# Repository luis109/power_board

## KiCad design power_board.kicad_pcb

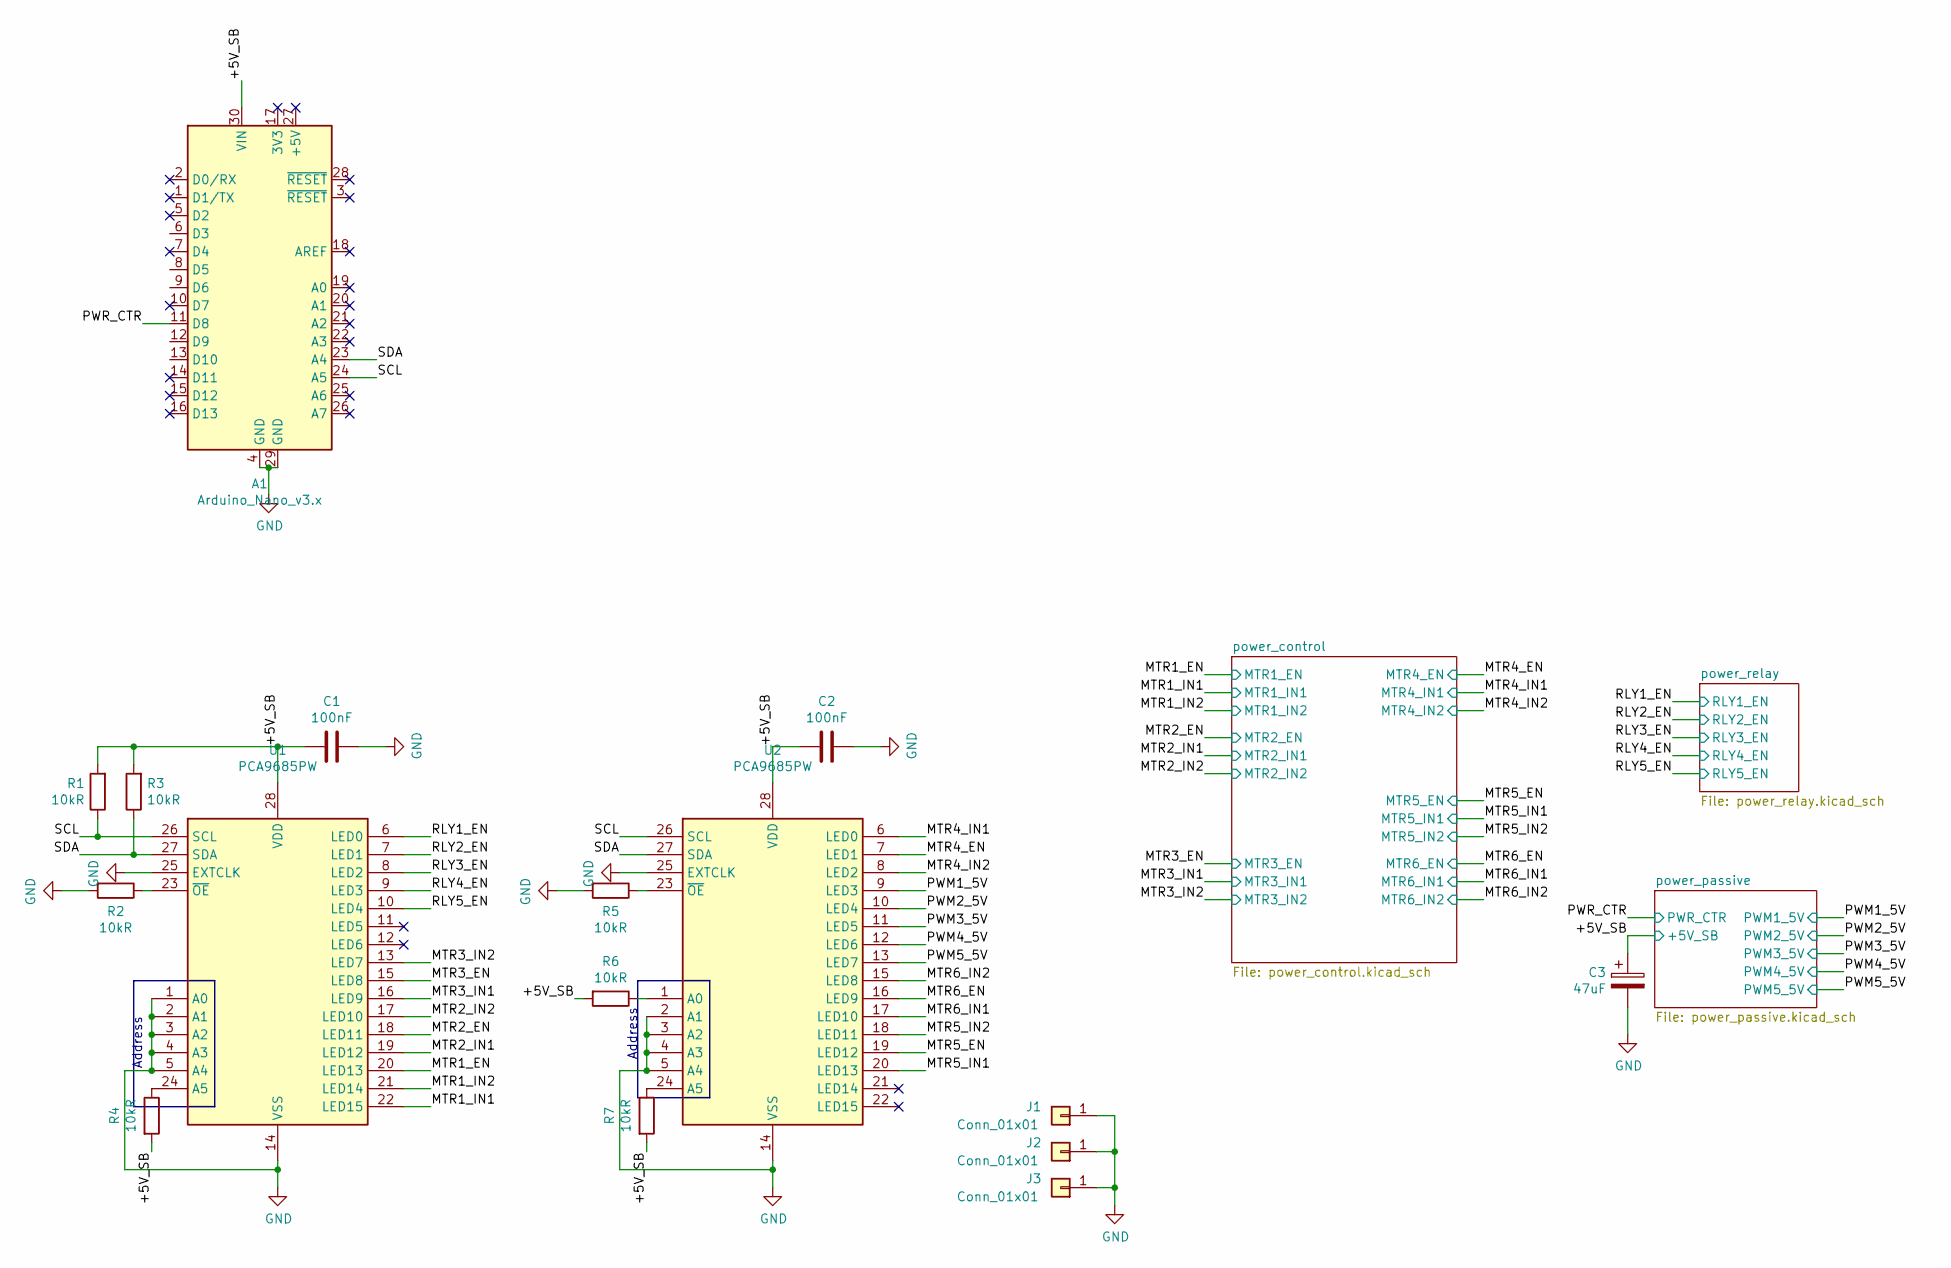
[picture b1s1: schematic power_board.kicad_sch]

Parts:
A1: Arduino_Nano_v3.x; Arduino_Nano
C1, C2: 100nF; C_0603
C3: 47uF; CP_Radial_D5.0mm_P2.00mm
J1, J2, J3: Conn_01x01; MountingHole_3.5mm_Pad
R1, R2, R3, R4, R5, R6, R7: 10kR; R_0603
U1, U2: PCA9685PW; TSSOP-28_4.4x9.7mm_P0.65mm

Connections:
/+5V_SB: A1.30 (VIN), C1.2, C2.2, C3.1, R1.2, R3.2, R4.2, R6.2, R7.2, U1.28 (VDD), U2.28 (VDD); also elsewhere on the board
/MTR1_EN: U1.20 (LED13); also elsewhere on the board
/MTR1_IN1: U1.22 (LED15); also elsewhere on the board
/MTR1_IN2: U1.21 (LED14); also elsewhere on the board
/MTR2_EN: U1.18 (LED11); also elsewhere on the board
/MTR2_IN1: U1.19 (LED12); also elsewhere on the board
/MTR2_IN2: U1.17 (LED10); also elsewhere on the board
/MTR3_EN: U1.15 (LED8); also elsewhere on the board
/MTR3_IN1: U1.16 (LED9); also elsewhere on the board
/MTR3_IN2: U1.13 (LED7); also elsewhere on the board
/MTR4_EN: U2.7 (LED1); also elsewhere on the board
/MTR4_IN1: U2.6 (LED0); also elsewhere on the board
/MTR4_IN2: U2.8 (LED2); also elsewhere on the board
/MTR5_EN: U2.19 (LED12); also elsewhere on the board
/MTR5_IN1: U2.20 (LED13); also elsewhere on the board
/MTR5_IN2: U2.18 (LED11); also elsewhere on the board
/MTR6_EN: U2.16 (LED9); also elsewhere on the board
/MTR6_IN1: U2.17 (LED10); also elsewhere on the board
/MTR6_IN2: U2.15 (LED8); also elsewhere on the board
/PWM1_5V: U2.9 (LED3); also elsewhere on the board
/PWM2_5V: U2.10 (LED4); also elsewhere on the board
/PWM3_5V: U2.11 (LED5); also elsewhere on the board
/PWM4_5V: U2.12 (LED6); also elsewhere on the board
/PWM5_5V: U2.13 (LED7); also elsewhere on the board
/PWR_CTR: A1.11 (D8); also elsewhere on the board
/RLY1_EN: U1.6 (LED0); also elsewhere on the board
/RLY2_EN: U1.7 (LED1); also elsewhere on the board
/RLY3_EN: U1.8 (LED2); also elsewhere on the board
/RLY4_EN: U1.9 (LED3); also elsewhere on the board
/RLY5_EN: U1.10 (LED4); also elsewhere on the board
/SCL: A1.24 (A5), R1.1, U1.26 (SCL), U2.26 (SCL)
/SDA: A1.23 (A4), R3.1, U1.27 (SDA), U2.27 (SDA)
GND: A1.4 (GND), A1.29 (GND), C1.1, C2.1, C3.2, J1.1, J2.1, J3.1, R2.2, R5.2, U1.1 (A0), U1.2 (A1), U1.3 (A2), U1.4 (A3), U1.5 (A4), U1.14 (VSS), U1.25 (EXTCLK), U2.2 (A1), U2.3 (A2), U2.4 (A3), U2.5 (A4), U2.14 (VSS), U2.25 (EXTCLK); also elsewhere on the board
unnamed: R2.1, U1.23 (~OE)
unnamed: R4.1, U1.24 (A5)
unnamed: R5.1, U2.23 (~OE)
unnamed: R6.1, U2.1 (A0)
unnamed: R7.1, U2.24 (A5)

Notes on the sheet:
Address

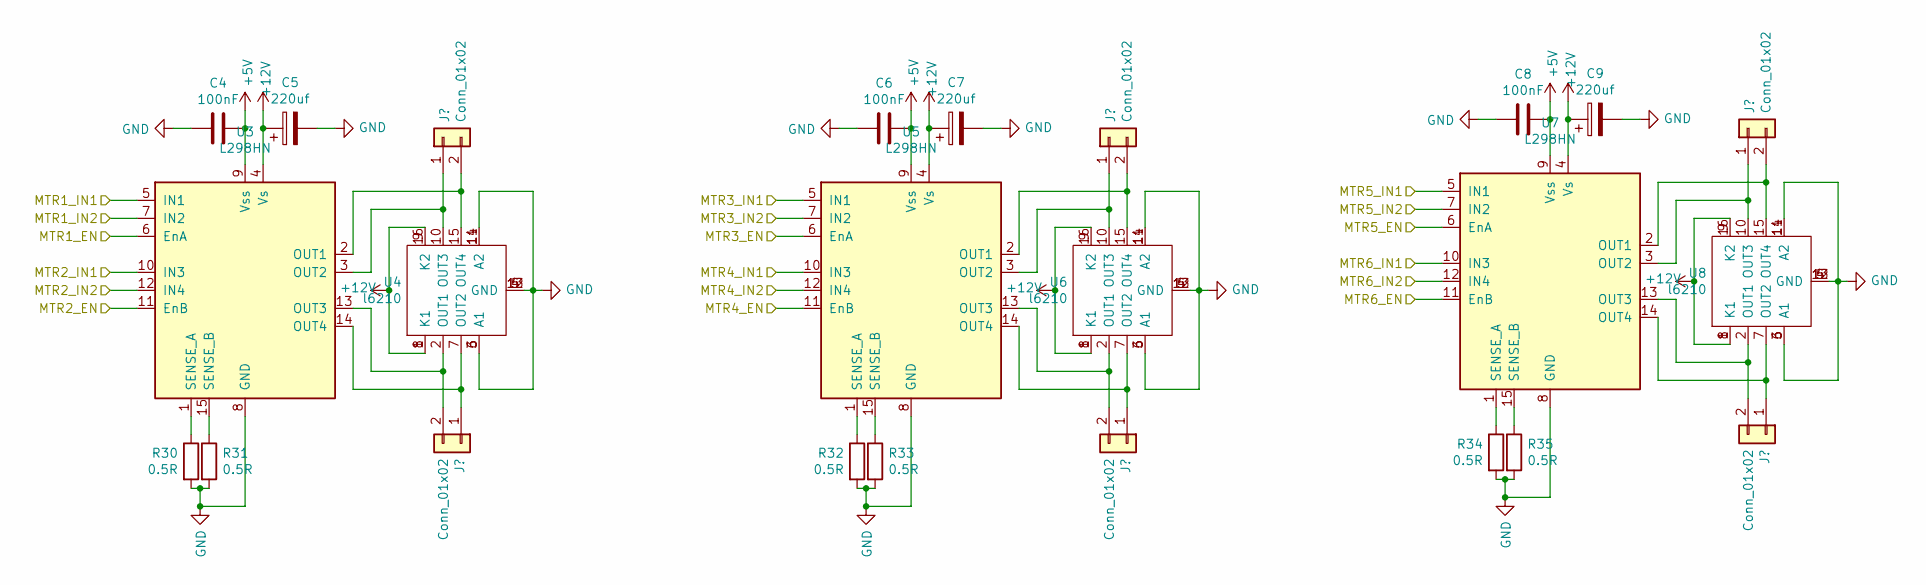
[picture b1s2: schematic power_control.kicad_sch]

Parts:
C4, C6, C8: 100nF; C_0603
C5, C7, C9: 220uf; CP_Radial_D10.0mm_P5.00mm
J25, J26, J27, J28, J29, J30: Conn_01x02; Molex_Micro-Fit_3.0_43045-0212_2x01_P3.00mm_Vertical
R30, R31, R32, R33, R34, R35: 0.5R; R_0805
U3, U5, U7: L298HN; TO-220-15_P2.54x2.54mm_StaggerOdd_Lead4.58mm_Vertical
U4, U6, U8: l6210; DIP-16_W7.62mm

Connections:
+5V: C4.1, C6.1, C8.1, U3.9 (Vss), U5.9 (Vss), U7.9 (Vss); also elsewhere on the board
+12V: C5.1, C7.1, C9.1, U3.4 (Vs), U4.1 (K1), U4.8 (K1), U4.9 (K2), U4.16 (K2), U5.4 (Vs), U6.1 (K1), U6.8 (K1), U6.9 (K2), U6.16 (K2), U7.4 (Vs), U8.1 (K1), U8.8 (K1), U8.9 (K2), U8.16 (K2); also elsewhere on the board
/MTR1_EN: U3.6 (EnA); also elsewhere on the board
/MTR1_IN1: U3.5 (IN1); also elsewhere on the board
/MTR1_IN2: U3.7 (IN2); also elsewhere on the board
/MTR2_EN: U3.11 (EnB); also elsewhere on the board
/MTR2_IN1: U3.10 (IN3); also elsewhere on the board
/MTR2_IN2: U3.12 (IN4); also elsewhere on the board
/MTR3_EN: U5.6 (EnA); also elsewhere on the board
/MTR3_IN1: U5.5 (IN1); also elsewhere on the board
/MTR3_IN2: U5.7 (IN2); also elsewhere on the board
/MTR4_EN: U5.11 (EnB); also elsewhere on the board
/MTR4_IN1: U5.10 (IN3); also elsewhere on the board
/MTR4_IN2: U5.12 (IN4); also elsewhere on the board
/MTR5_EN: U7.6 (EnA); also elsewhere on the board
/MTR5_IN1: U7.5 (IN1); also elsewhere on the board
/MTR5_IN2: U7.7 (IN2); also elsewhere on the board
/MTR6_EN: U7.11 (EnB); also elsewhere on the board
/MTR6_IN1: U7.10 (IN3); also elsewhere on the board
/MTR6_IN2: U7.12 (IN4); also elsewhere on the board
GND: C4.2, C5.2, C6.2, C7.2, C8.2, C9.2, R30.2, R31.2, R32.2, R33.2, R34.2, R35.2, U3.8 (GND), U4.3 (A1), U4.4 (GND), U4.5 (GND), U4.6 (A1), U4.11 (A2), U4.12 (GND), U4.13 (GND), U4.14 (A2), U5.8 (GND), U6.3 (A1), U6.4 (GND), U6.5 (GND), U6.6 (A1), U6.11 (A2), U6.12 (GND), U6.13 (GND), U6.14 (A2), U7.8 (GND), U8.3 (A1), U8.4 (GND), U8.5 (GND), U8.6 (A1), U8.11 (A2), U8.12 (GND), U8.13 (GND), U8.14 (A2); also elsewhere on the board
unnamed: J25.1, U3.3 (OUT2), U4.10 (OUT3)
unnamed: J25.2, U3.2 (OUT1), U4.15 (OUT4)
unnamed: J26.1, U3.14 (OUT4), U4.7 (OUT2)
unnamed: J26.2, U3.13 (OUT3), U4.2 (OUT1)
unnamed: J27.1, U5.3 (OUT2), U6.10 (OUT3)
unnamed: J27.2, U5.2 (OUT1), U6.15 (OUT4)
unnamed: J28.1, U5.14 (OUT4), U6.7 (OUT2)
unnamed: J28.2, U5.13 (OUT3), U6.2 (OUT1)
unnamed: J29.1, U7.3 (OUT2), U8.10 (OUT3)
unnamed: J29.2, U7.2 (OUT1), U8.15 (OUT4)
unnamed: J30.1, U7.14 (OUT4), U8.7 (OUT2)
unnamed: J30.2, U7.13 (OUT3), U8.2 (OUT1)
unnamed: R30.1, U3.1 (SENSE_A)
unnamed: R31.1, U3.15 (SENSE_B)
unnamed: R32.1, U5.1 (SENSE_A)
unnamed: R33.1, U5.15 (SENSE_B)
unnamed: R34.1, U7.1 (SENSE_A)
unnamed: R35.1, U7.15 (SENSE_B)

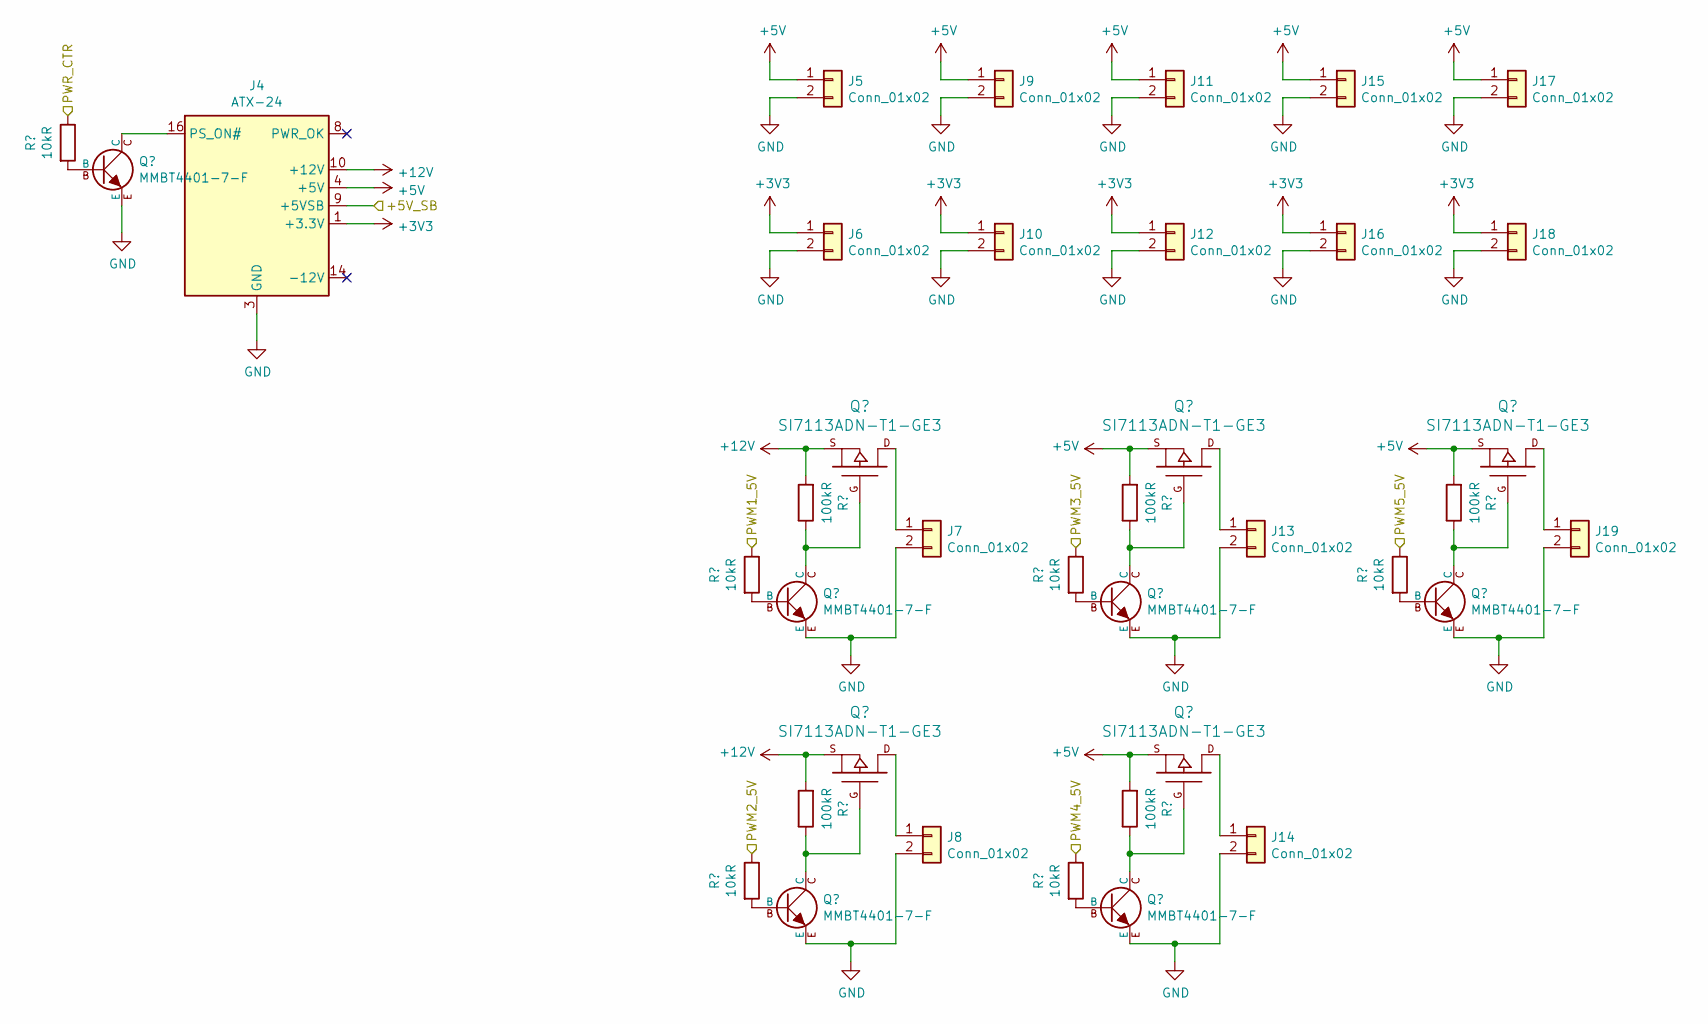
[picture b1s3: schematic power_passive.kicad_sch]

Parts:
J4: ATX-24; Molex_Mini-Fit_Jr_5566-24A_2x12_P4.20mm_Vertical
J5, J6, J7, J8, J9, J10, J11, J12, J13, J14, J15, J16, J17, J18, J19: Conn_01x02; Molex_Micro-Fit_3.0_43045-0212_2x01_P3.00mm_Vertical
Q1, Q2, Q3, Q6, Q7, Q10: MMBT4401-7-F; SOT23_BC817
Q4, Q5, Q8, Q9, Q11: SI7113ADN-T1-GE3; PowerPAK_1212-8
R8, R10, R11, R14, R15, R18: 10kR; R_0603
R12, R13, R16, R17, R19: 100kR; R_0603

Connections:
+3V3: J4.1 (+3.3V), J4.2 (+3.3V), J4.12 (+3.3V), J4.13 (+3.3V), J6.1, J10.1, J12.1, J16.1, J18.1
+5V: J4.4 (+5V), J4.6 (+5V), J4.21 (+5V), J4.22 (+5V), J4.23 (+5V), J5.1, J9.1, J11.1, J15.1, J17.1, Q8.S, Q9.S, Q11.S, R16.2, R17.2, R19.2; also elsewhere on the board
+12V: J4.10 (+12V), J4.11 (+12V), Q4.S, Q5.S, R12.2, R13.2; also elsewhere on the board
/+5V_SB: J4.9 (+5VSB); also elsewhere on the board
/PWM1_5V: R10.1; also elsewhere on the board
/PWM2_5V: R11.1; also elsewhere on the board
/PWM3_5V: R14.1; also elsewhere on the board
/PWM4_5V: R15.1; also elsewhere on the board
/PWM5_5V: R18.1; also elsewhere on the board
/PWR_CTR: R8.1; also elsewhere on the board
GND: J4.3 (GND), J4.5 (GND), J4.7 (GND), J4.15 (GND), J4.17 (GND), J4.18 (GND), J4.19 (GND), J4.24 (GND), J5.2, J6.2, J7.2, J8.2, J9.2, J10.2, J11.2, J12.2, J13.2, J14.2, J15.2, J16.2, J17.2, J18.2, J19.2, Q1.E, Q2.E, Q3.E, Q6.E, Q7.E, Q10.E; also elsewhere on the board
unnamed: J4.16 (PS_ON#), Q1.C
unnamed: J7.1, Q4.D
unnamed: J8.1, Q5.D
unnamed: J13.1, Q8.D
unnamed: J14.1, Q9.D
unnamed: J19.1, Q11.D
unnamed: Q1.B, R8.2
unnamed: Q2.B, R10.2
unnamed: Q2.C, Q4.G, R12.1
unnamed: Q3.B, R11.2
unnamed: Q3.C, Q5.G, R13.1
unnamed: Q6.B, R14.2
unnamed: Q6.C, Q8.G, R16.1
unnamed: Q7.B, R15.2
unnamed: Q7.C, Q9.G, R17.1
unnamed: Q10.B, R18.2
unnamed: Q10.C, Q11.G, R19.1

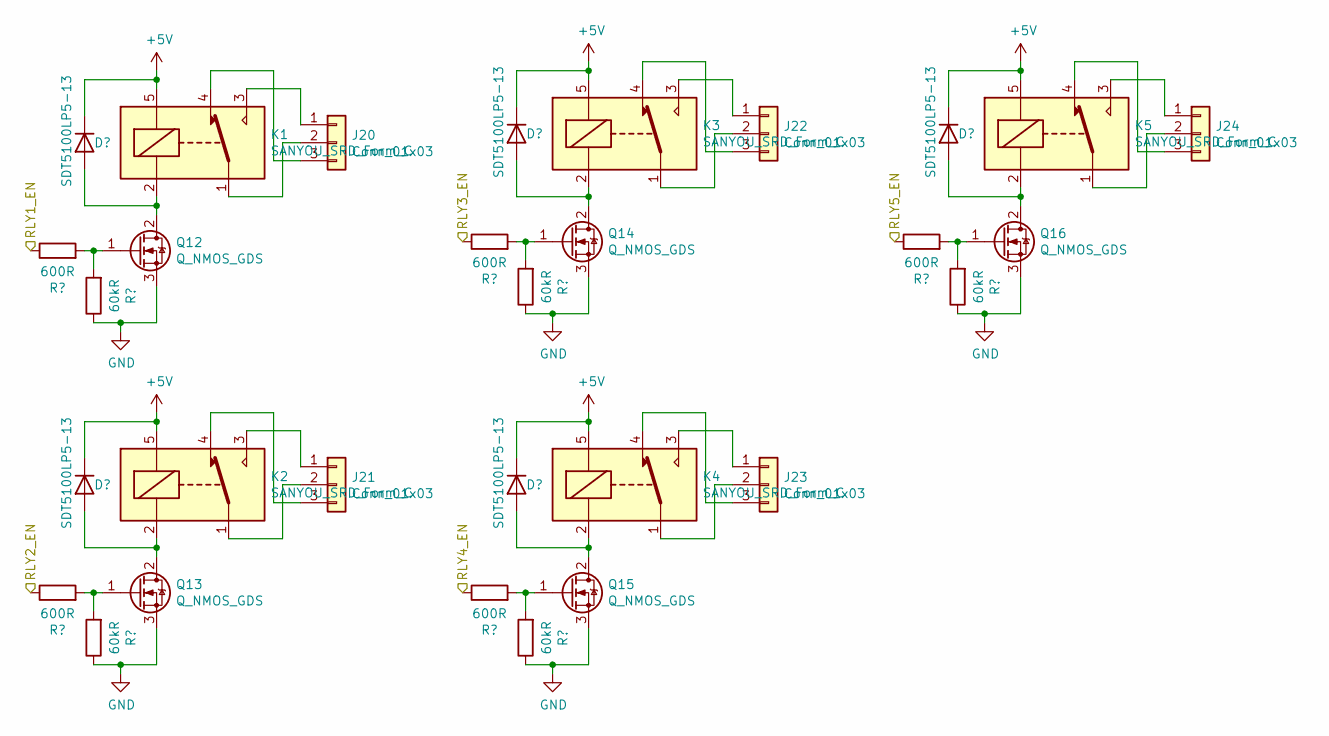
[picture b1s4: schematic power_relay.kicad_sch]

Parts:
D1, D2, D3, D4, D5: SDT5100LP5-13; D_PowerDI-5
J20, J21, J22, J23, J24: Conn_01x03; TerminalBlock_Phoenix_PT-1,5-3-3.5-H_1x03_P3.50mm_Horizontal
K1, K2, K3, K4, K5: SANYOU_SRD_Form_C; Relay_SPDT_SANYOU_SRD_Series_Form_C
Q12, Q13, Q14, Q15, Q16: Q_NMOS_GDS; TO-252-2
R20, R21, R24, R25, R28: 600R; R_0603
R22, R23, R26, R27, R29: 60kR; R_0603

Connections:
+5V: D1.1 (K), D2.1 (K), D3.1 (K), D4.1 (K), D5.1 (K), K1.5, K2.5, K3.5, K4.5, K5.5; also elsewhere on the board
/RLY1_EN: R20.1; also elsewhere on the board
/RLY2_EN: R21.1; also elsewhere on the board
/RLY3_EN: R24.1; also elsewhere on the board
/RLY4_EN: R25.1; also elsewhere on the board
/RLY5_EN: R28.1; also elsewhere on the board
GND: Q12.3 (S), Q13.3 (S), Q14.3 (S), Q15.3 (S), Q16.3 (S), R22.1, R23.1, R26.1, R27.1, R29.1; also elsewhere on the board
unnamed: D1.2 (A), K1.2, Q12.2 (D)
unnamed: D2.2 (A), K2.2, Q13.2 (D)
unnamed: D3.2 (A), K3.2, Q14.2 (D)
unnamed: D4.2 (A), K4.2, Q15.2 (D)
unnamed: D5.2 (A), K5.2, Q16.2 (D)
unnamed: J20.1, K1.3
unnamed: J20.2, K1.1
unnamed: J20.3, K1.4
unnamed: J21.1, K2.3
unnamed: J21.2, K2.1
unnamed: J21.3, K2.4
unnamed: J22.1, K3.3
unnamed: J22.2, K3.1
unnamed: J22.3, K3.4
unnamed: J23.1, K4.3
unnamed: J23.2, K4.1
unnamed: J23.3, K4.4
unnamed: J24.1, K5.3
unnamed: J24.2, K5.1
unnamed: J24.3, K5.4
unnamed: Q12.1 (G), R20.2, R22.2
unnamed: Q13.1 (G), R21.2, R23.2
unnamed: Q14.1 (G), R24.2, R26.2
unnamed: Q15.1 (G), R25.2, R27.2
unnamed: Q16.1 (G), R28.2, R29.2

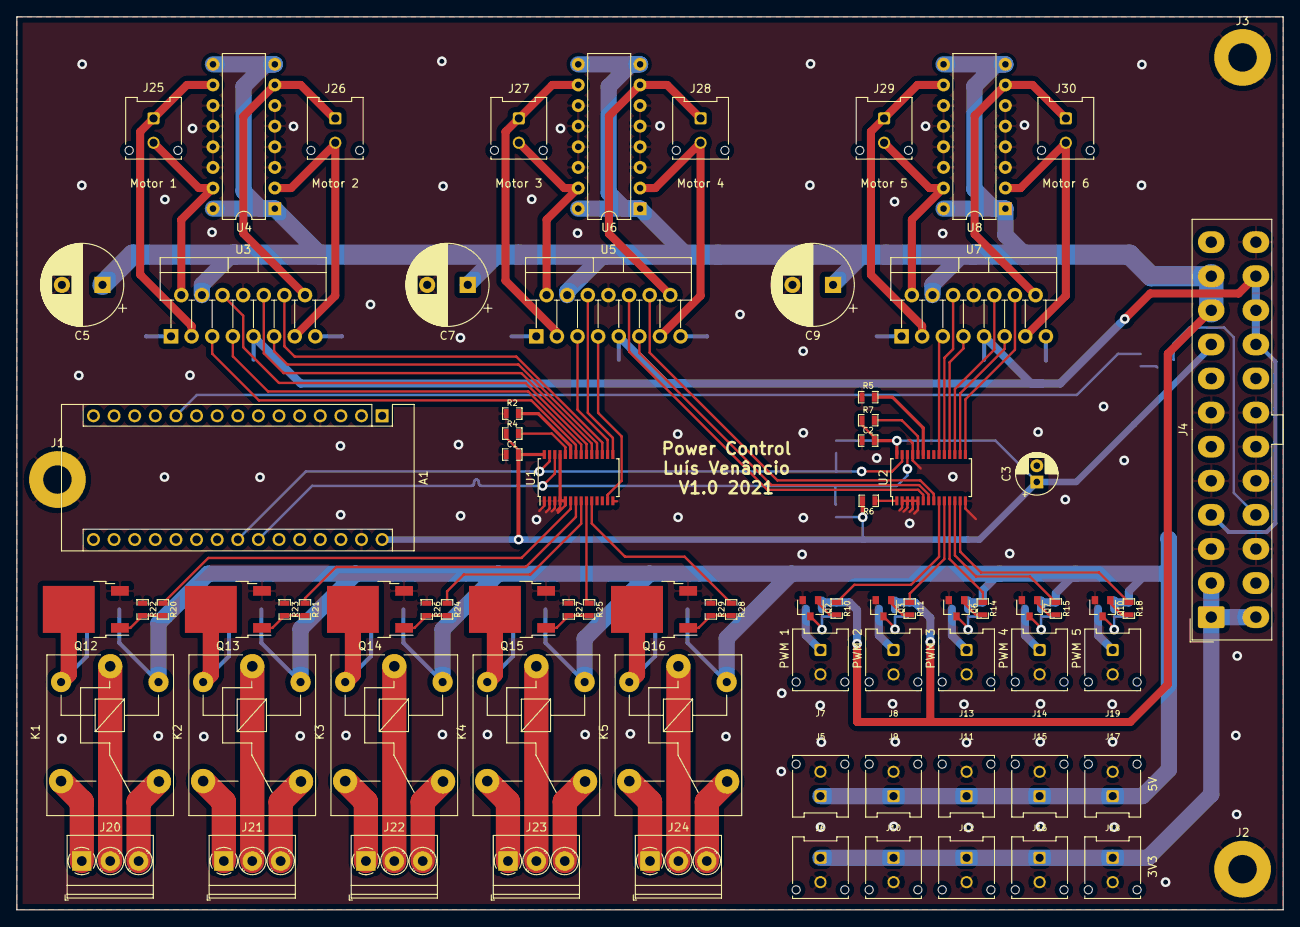
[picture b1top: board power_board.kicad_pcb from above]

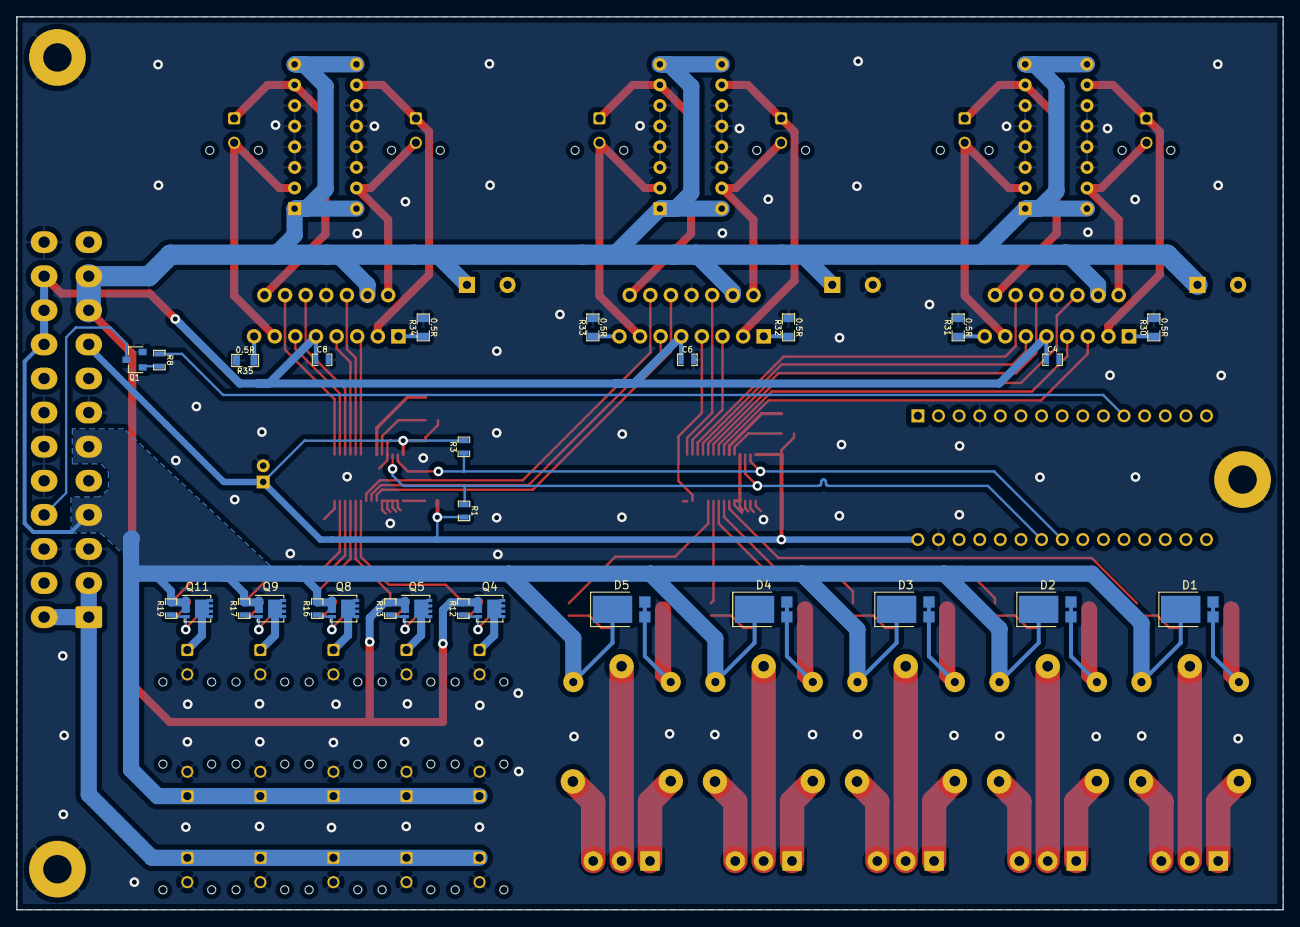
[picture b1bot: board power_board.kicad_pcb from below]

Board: 2 copper layers, 156.0 x 110.0 mm, 108 parts (28 on the bottom side), 101 nets.

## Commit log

2020-01-17 Motor control positioning
2020-01-20 Motor control finished
2020-01-20 PWM entries positioning
2020-01-20 Power wiring finished
2020-01-20 Initial attempt
2020-01-21 Almost
2020-01-22 Template
2020-01-22 All blocks aligned
2020-01-22 Positioning finished
    Lacks fine alignment.
2020-01-22 Start MCU layout
2020-01-23 Fine tune position. Power lines mtr and passive.
2020-01-23 Initial MCU positioning. Reassign LED.
2020-01-23 ATX to right side
2020-01-24 Stash
2020-01-27 ICs positioning
2020-01-27 I2C lines positioned and tunned
2020-01-27 All components placed.
2020-01-27 Zones filled
2020-01-28 All connections complete
2020-01-29 Silkscreen done
2020-01-30 Added 47uF electrolytic capacitor to 5V_SB.
2020-01-31 Added capacitor references
2020-02-04 Added remaining 0603 references
2020-02-05 Changed "out of stock" references.
2020-02-28 Removed L6203
2020-03-02 Added DRV8801PWP to schematic
2020-03-02 Footprint configuration
2020-03-03 Initial board placement.
2020-03-03 Replaced FTDI placement.
2020-03-04 Routing.
2020-03-05 New driver arrangement
2020-03-07 Driver control routed
2020-03-07 Finished connections
2020-03-10 Finished silkscreen.
2020-03-14 Improvements
2020-03-21 Small changes and added labels
2020-03-22 Removed PCA9555 and added PCA9685
2020-03-22 Increased motor connectors distance to board edge
2020-03-22 Reroute ISP
2020-04-05 Changed ATX-24 symbol to merged version.
2020-05-27 Switch PMW 1 & 2 to 12V
2021-06-03 Replaced MCU by Arduino Nano
2021-07-13 Final touches
2021-11-04 Replaced motor drivers
2022-01-02 Replaced driver footprints
2022-01-03 Added 220uf capacitors
2022-01-04 Changed general footprint placement and added vias
2022-05-10 Changed sense resistor footprint
2022-12-02 Small fix
2023-03-23 Ported to Kicad V7
